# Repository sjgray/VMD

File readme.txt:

VMD - Visual Memory Display - Steve J. Gray
===========================

INTRO

This is a fun little project, probably not with many practical uses,
other than being a cool blinking lights display. On the CBM-Hackers
forum Leif Bloomquist proposed the idea of adding interesting lights
inside his transparent C64 case to show computer activity. I came up
with an idea to use a large 16x16 LED matrix wired to the address
bus using some 4-to-16 decoders. Jim Brain liked the idea and said
he would build it, and he did. He came up with a circuit which he
demonstrated at the VCF-MW show in September 2016. I am attempting to
design a PCB or two to implement this internally.

STATUS

The project is functional. This version is the initial proof of concept
design, not created for any specific LED matrix modules. You will need
to look at the datasheet for your module and figure out how to connect
them. The COL pins are the + (anode) of the LED and the ROW are the cathode.

I was hoping to improve the design, and/or adapt it to some specific LED
module to make connections easier, but the project seems to have been
put on the back-burner. So, I am releasing the schematics and gerbers
as-is in the hopes that it might be useful.

FOLDERS

VMD.......... Main Visual Memory Display board
CPU-Tap...... 6502/6510 breakout board with VMD connectors.
		tabs can be removed if you just need the breakout pins.
MemoryMaps... Memory Maps for CBM computers using 16x16 matrix organization

WEB

You can find more info on the project webpage:

http://www.cbmsteve.ca/
http://www.cbmsteve.ca/vmd/index.html

Steve

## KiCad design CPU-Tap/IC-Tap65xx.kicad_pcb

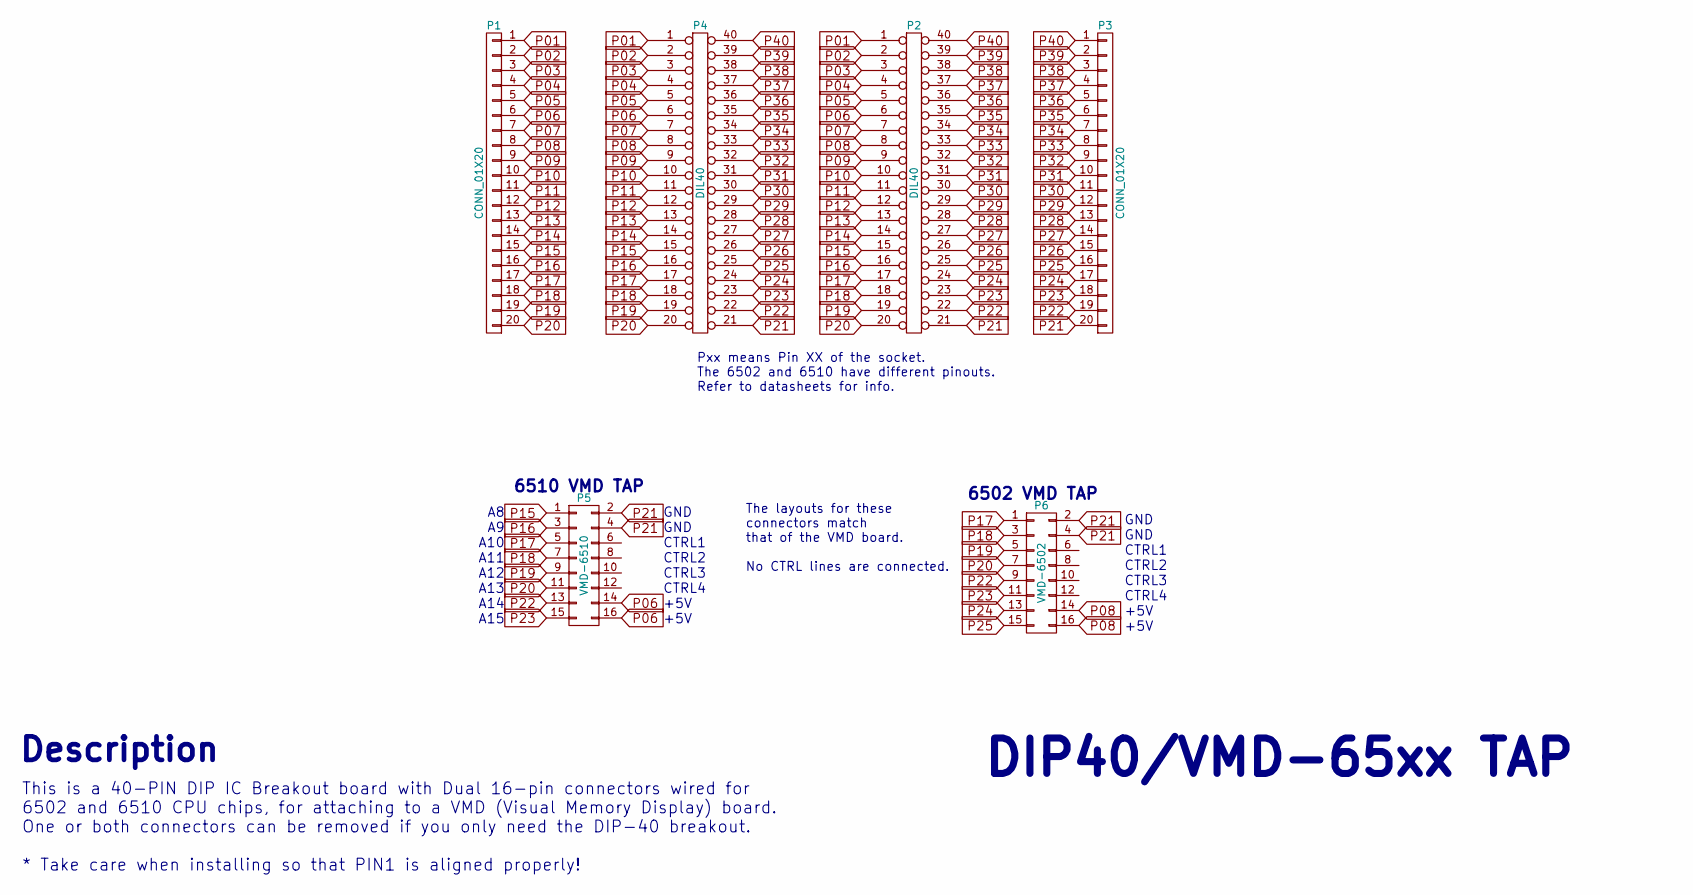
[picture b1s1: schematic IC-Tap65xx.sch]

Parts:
P1, P3: CONN_01X20; Pin_Header_Straight_1x20
P2, P4: DIL40; DIP-40_W15.24mm_LongPads
P5: VMD-6510; Pin_Header_Straight_2x08
P6: VMD-6502; Pin_Header_Straight_2x08

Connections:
P01: P1.1, P2.1, P4.1
P02: P1.2, P2.2, P4.2
P03: P1.3, P2.3, P4.3
P04: P1.4, P2.4, P4.4
P05: P1.5, P2.5, P4.5
P06: P1.6, P2.6, P4.6, P5.14, P5.16
P07: P1.7, P2.7, P4.7
P08: P1.8, P2.8, P4.8, P6.14, P6.16
P09: P1.9, P2.9, P4.9
P10: P1.10, P2.10, P4.10
P11: P1.11, P2.11, P4.11
P12: P1.12, P2.12, P4.12
P13: P1.13, P2.13, P4.13
P14: P1.14, P2.14, P4.14
P15: P1.15, P2.15, P4.15, P5.1
P16: P1.16, P2.16, P4.16, P5.3
P17: P1.17, P2.17, P4.17, P5.5, P6.1
P18: P1.18, P2.18, P4.18, P5.7, P6.3
P19: P1.19, P2.19, P4.19, P5.9, P6.5
P20: P1.20, P2.20, P4.20, P5.11, P6.7
P21: P2.21, P3.20, P4.21, P5.2, P5.4, P6.2, P6.4
P22: P2.22, P3.19, P4.22, P5.13, P6.9
P23: P2.23, P3.18, P4.23, P5.15, P6.11
P24: P2.24, P3.17, P4.24, P6.13
P25: P2.25, P3.16, P4.25, P6.15
P26: P2.26, P3.15, P4.26
P27: P2.27, P3.14, P4.27
P28: P2.28, P3.13, P4.28
P29: P2.29, P3.12, P4.29
P30: P2.30, P3.11, P4.30
P31: P2.31, P3.10, P4.31
P32: P2.32, P3.9, P4.32
P33: P2.33, P3.8, P4.33
P34: P2.34, P3.7, P4.34
P35: P2.35, P3.6, P4.35
P36: P2.36, P3.5, P4.36
P37: P2.37, P3.4, P4.37
P38: P2.38, P3.3, P4.38
P39: P2.39, P3.2, P4.39
P40: P2.40, P3.1, P4.40

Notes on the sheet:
A8 A9 A10 A11 A12 A13 A14 A15
GND GND CTRL1 CTRL2 CTRL3 CTRL4 +5V +5V
6510 VMD TAP
6502 VMD TAP
Pxx means Pin XX of the socket. The 6502 and 6510 have different pinouts. Refer to datasheets for info.
The layouts for these connectors match that of the VMD board. No CTRL lines are connected.
DIP40/VMD-65xx TAP
This is a 40-PIN DIP IC Breakout board with Dual 16-pin connectors wired for 6502 and 6510 CPU chips, for attaching to a VMD (Visual Memory Display) board. One or both connectors can be removed if you only need the DIP-40 breakout. * Take care when installing so that PIN1 is aligned properly!
Description

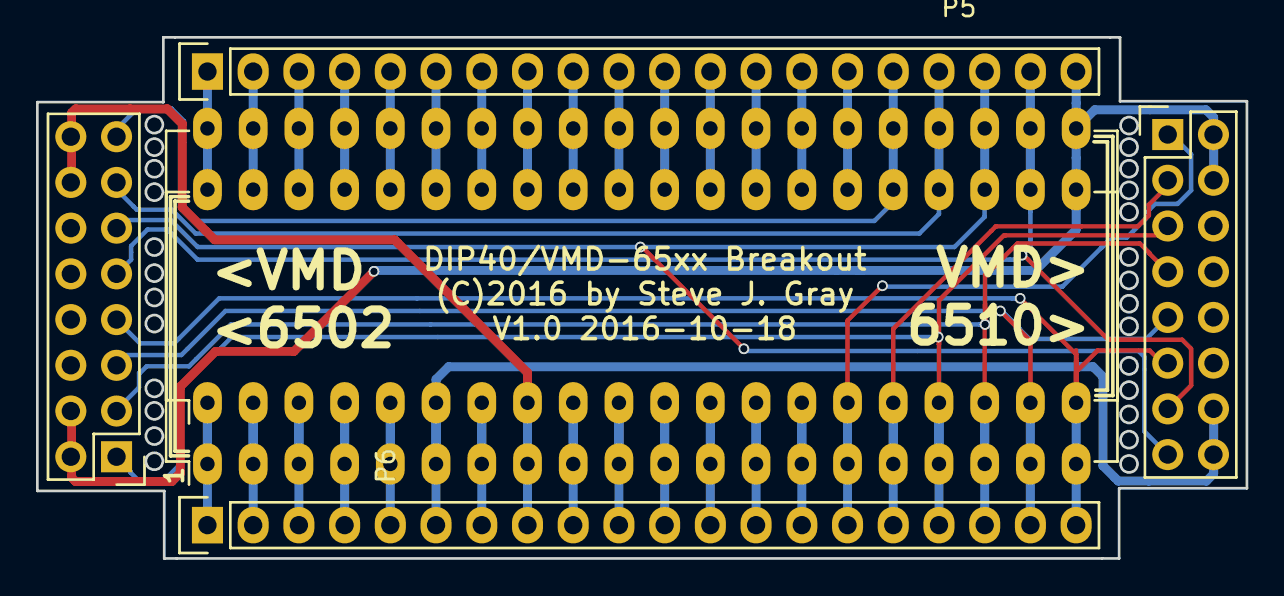
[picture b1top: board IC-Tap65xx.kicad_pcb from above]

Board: 2 copper layers, 67.2 x 29.0 mm, 6 parts (0 on the bottom side), 40 nets.

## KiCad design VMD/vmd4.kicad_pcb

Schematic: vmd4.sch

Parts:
C1, C2, C3, C4, C5, C6, C7, C8, C9: .1; C_Disc_D3_P2.5
P1: CONN_02X08; Pin_Header_Straight_2x08
P2: CONN_02X04; Pin_Header_Straight_2x04
P3, P4: ROW 0-7; Pin_Header_Straight_1x08
P5, P6: ROW 8-15; Pin_Header_Straight_1x08
P7, P8, P9, P10: COL 0-7; Pin_Header_Straight_1x08
P11: CONN_01X02; Pin_Header_Straight_1x02
R1, R2, R3, R4: R_Small; Resistor_Horizontal_RM7mm
RP1, RP2: 220 ohm; DIP-16_W7.62mm_LongPads
S1: SW_DIP_x4; SW_DIP_x4_Slide
U1, U3, U5, U7: 74LS138; DIP-16_W7.62mm_LongPads
U2, U4, U6, U8: 74LS541; DIP-20_W7.62mm_LongPads
U9: 74LS86; DIP-14_W7.62mm_LongPads

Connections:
5V: C1.1, C2.1, C3.1, C4.1, C5.1, C6.1, C7.1, C8.1, C9.1, P1.14, P1.16, P11.1, R1.1, R2.1, R3.1, R4.1, U1.6 (E3), U1.16 (VCC), U2.20 (VCC), U3.16 (VCC), U4.20 (VCC), U5.6 (E3), U5.16 (VCC), U6.20 (VCC), U7.16 (VCC), U8.20 (VCC), U9.14 (VCC)
A8: P1.1, U5.1 (A0), U7.1 (A0)
A9: P1.3, U5.2 (A1), U7.2 (A1)
A10: P1.5, U5.3 (A2), U7.3 (A2)
A11: P1.7, U5.5 (E2), U7.6 (E3)
A12: P1.9, U1.1 (A0), U3.1 (A0)
A13: P1.11, U1.2 (A1), U3.2 (A1)
A14: P1.13, U1.3 (A2), U3.3 (A2)
A15: P1.15, U1.5 (E2), U3.6 (E3)
C0: P7.1, P8.1, RP1.16 (R1)
C1: P7.2, P8.2, RP1.15 (R2)
C2: P7.3, P8.3, RP1.14 (R3)
C3: P7.4, P8.4, RP1.13 (R4)
C4: P7.5, P8.5, RP1.12 (R5)
C5: P7.6, P8.6, RP1.11 (R6)
C6: P7.7, P8.7, RP1.10 (R7)
C7: P7.8, P8.8, RP1.9 (R8)
C8: P9.1, P10.1, RP2.16 (R1)
C9: P9.2, P10.2, RP2.15 (R2)
C10: P9.3, P10.3, RP2.14 (R3)
C11: P9.4, P10.4, RP2.13 (R4)
C12: P9.5, P10.5, RP2.12 (R5)
C13: P9.6, P10.6, RP2.11 (R6)
C14: P9.7, P10.7, RP2.10 (R7)
C15: P9.8, P10.8, RP2.9 (R8)
CTRL1: P1.6, P2.2, U9.2 (IN2)
CTRL2: P1.8, P2.4, U9.5 (IN2)
CTRL3: P1.10, P2.6, U9.10 (IN2)
CTRL4: P1.12, P2.8, U9.13 (IN2)
G1: U2.1 (G1), U4.1 (G1), U9.3 (OUT)
G2: U2.19 (G2), U4.19 (G2), U9.6 (OUT)
G3: U6.1 (G1), U8.1 (G1), U9.8 (OUT)
G4: U6.19 (G2), U8.19 (G2), U9.11 (OUT)
GND: C1.2, C2.2, C3.2, C4.2, C5.2, C6.2, C7.2, C8.2, C9.2, P1.2, P1.4, P2.1, P2.3, P2.5, P2.7, P11.2, S1.1, S1.2, S1.3, S1.4, U1.4 (E1), U1.8 (GND), U2.10 (GND), U3.4 (E1), U3.5 (E2), U3.8 (GND), U4.10 (GND), U5.4 (E1), U5.8 (GND), U6.10 (GND), U7.4 (E1), U7.5 (E2), U7.8 (GND), U8.10 (GND), U9.7 (GND)
unnamed: R1.2, S1.5, U9.12 (IN1)
unnamed: R2.2, S1.6, U9.9 (IN1)
unnamed: R3.2, S1.7, U9.4 (IN1)
unnamed: R4.2, S1.8, U9.1 (IN1)
unnamed: RP1.1, U6.18 (Y0)
unnamed: RP1.2, U6.17 (Y1)
unnamed: RP1.3, U6.16 (Y2)
unnamed: RP1.4, U6.15 (Y3)
unnamed: RP1.5, U6.14 (Y4)
unnamed: RP1.6, U6.13 (Y5)
unnamed: RP1.7, U6.12 (Y6)
unnamed: RP1.8, U6.11 (Y7)
unnamed: RP2.1, U8.18 (Y0)
unnamed: RP2.2, U8.17 (Y1)
unnamed: RP2.3, U8.16 (Y2)
unnamed: RP2.4, U8.15 (Y3)
unnamed: RP2.5, U8.14 (Y4)
unnamed: RP2.6, U8.13 (Y5)
unnamed: RP2.7, U8.12 (Y6)
unnamed: RP2.8, U8.11 (Y7)
unnamed: U1.7 (O7), U2.9 (A7)
unnamed: U1.9 (O6), U2.8 (A6)
unnamed: U1.10 (O5), U2.7 (A5)
unnamed: U1.11 (O4), U2.6 (A4)
unnamed: U1.12 (O3), U2.5 (A3)
unnamed: U1.13 (O2), U2.4 (A2)
unnamed: U1.14 (O1), U2.3 (A1)
unnamed: U1.15 (O0), U2.2 (A0)
unnamed: U3.7 (O7), U4.9 (A7)
unnamed: U3.9 (O6), U4.8 (A6)
unnamed: U3.10 (O5), U4.7 (A5)
unnamed: U3.11 (O4), U4.6 (A4)
unnamed: U3.12 (O3), U4.5 (A3)
unnamed: U3.13 (O2), U4.4 (A2)
unnamed: U3.14 (O1), U4.3 (A1)
unnamed: U3.15 (O0), U4.2 (A0)
unnamed: U5.7 (O7), U6.9 (A7)
unnamed: U5.9 (O6), U6.8 (A6)
unnamed: U5.10 (O5), U6.7 (A5)
unnamed: U5.11 (O4), U6.6 (A4)
unnamed: U5.12 (O3), U6.5 (A3)
unnamed: U5.13 (O2), U6.4 (A2)
unnamed: U5.14 (O1), U6.3 (A1)
unnamed: U5.15 (O0), U6.2 (A0)
unnamed: U7.7 (O7), U8.9 (A7)
unnamed: U7.9 (O6), U8.8 (A6)
unnamed: U7.10 (O5), U8.7 (A5)
unnamed: U7.11 (O4), U8.6 (A4)
unnamed: U7.12 (O3), U8.5 (A3)
unnamed: U7.13 (O2), U8.4 (A2)
unnamed: U7.14 (O1), U8.3 (A1)
unnamed: U7.15 (O0), U8.2 (A0)
R0: P3.1, P4.1, U2.18 (Y0)
R1: P3.2, P4.2, U2.17 (Y1)
R2: P3.3, P4.3, U2.16 (Y2)
R3: P3.4, P4.4, U2.15 (Y3)
R4: P3.5, P4.5, U2.14 (Y4)
R5: P3.6, P4.6, U2.13 (Y5)
R6: P3.7, P4.7, U2.12 (Y6)
R7: P3.8, P4.8, U2.11 (Y7)
R8: P5.1, P6.1, U4.18 (Y0)
R9: P5.2, P6.2, U4.17 (Y1)
R10: P5.3, P6.3, U4.16 (Y2)
R11: P5.4, P6.4, U4.15 (Y3)
R12: P5.5, P6.5, U4.14 (Y4)
R13: P5.6, P6.6, U4.13 (Y5)
R14: P5.7, P6.7, U4.12 (Y6)
R15: P5.8, P6.8, U4.11 (Y7)

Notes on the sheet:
LED VMD - Visual Memory Display
There are 4 Control lines - CTRL1 to CTRL4. Use DIP Switch to select if control lines trigger on HI or LO state. Unused control lines should be tied to GND or 5V and the matching DIP Switch line set accordingly.
Both "G" lines must be HI to enable output
74LS540
A15=HI >
A15=LO >
A11=LO >
A11=HI >
Based on an idea by Leif Bloomquist and Circuit by Jim Brain
There will be a companion CPU "tap" PCB with this same pinout.
On an 8-bit CPU there are 16 Address lines. The top 8 select one of 256 pages of memory, each containing 256 bytes. Of the top 8 bits we use 4 to select a ROW and 4 to select a COL. Each set of 4 lines is decoded to a single output by two 3-to-8 decoder chips. These are fed to a buffer chip that ca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
or use individual 220 ohm resitors
Circuit Description
Control
Decode
LED Drivers
LED Connectors
Unused CTRL
Optional Power
Jumper unused CTRL lines to GND
Can be used to power board from external 5V supply
Bypass caps

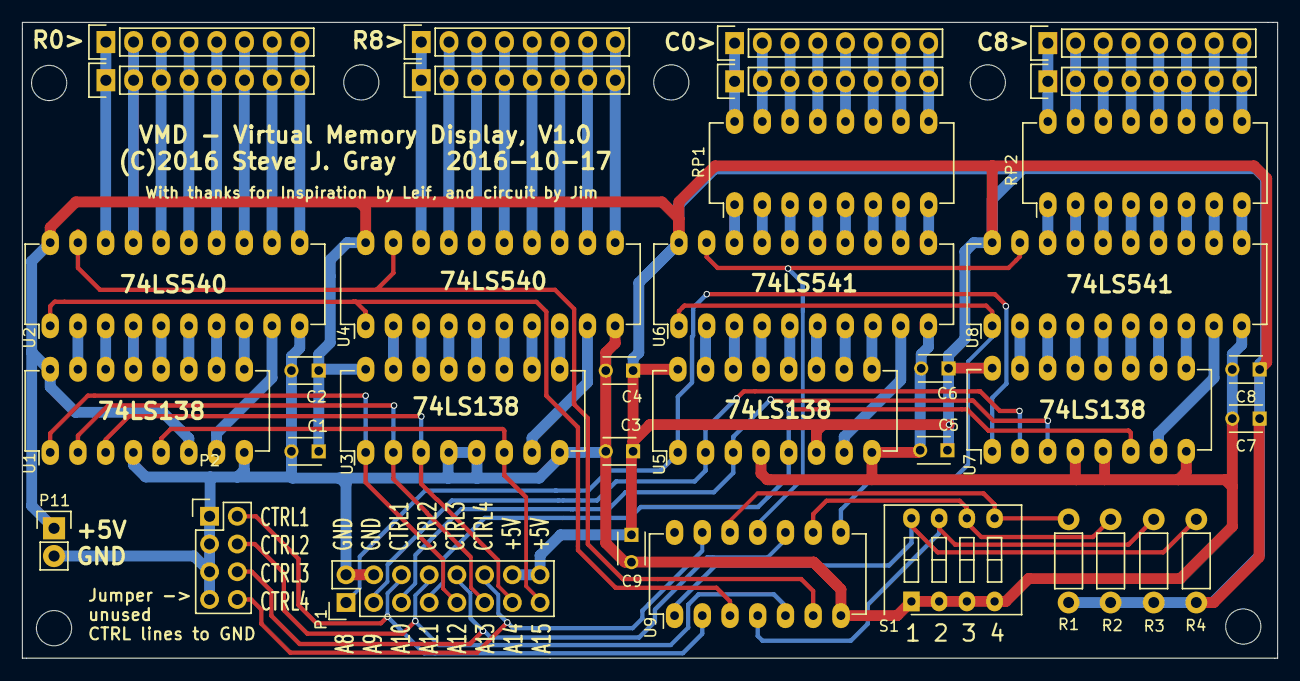
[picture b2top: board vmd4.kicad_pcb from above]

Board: 2 copper layers, 115.0 x 58.2 mm, 36 parts (0 on the bottom side), 102 nets.

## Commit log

2022-01-10 :lollipop: Added .gitattributes & .gitignore files
2022-01-10 Initial Commit.
    This is the initial working design Kicad files and Gerbers. The design
    is functional as a proof-of-concept. It is possible to modify the
    design with specific LED modules on the board if that is desired, but
    left up to you.
2022-02-02 Add CPU-Tap. Folder re-org
    Added CPU-Tap/breakout board for 6502/6510 processors. Move VMD board
    into folder.
2025-01-22 Chang webpage link
    cbmsteve.ca

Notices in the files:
CPU-Tap/IC-Tap65xx.kicad_pcb:
(C)2016 by Steve J. Gray
VMD/vmd4.kicad_pcb:
(C)2016 Steve J. Gray 2016-10-17
